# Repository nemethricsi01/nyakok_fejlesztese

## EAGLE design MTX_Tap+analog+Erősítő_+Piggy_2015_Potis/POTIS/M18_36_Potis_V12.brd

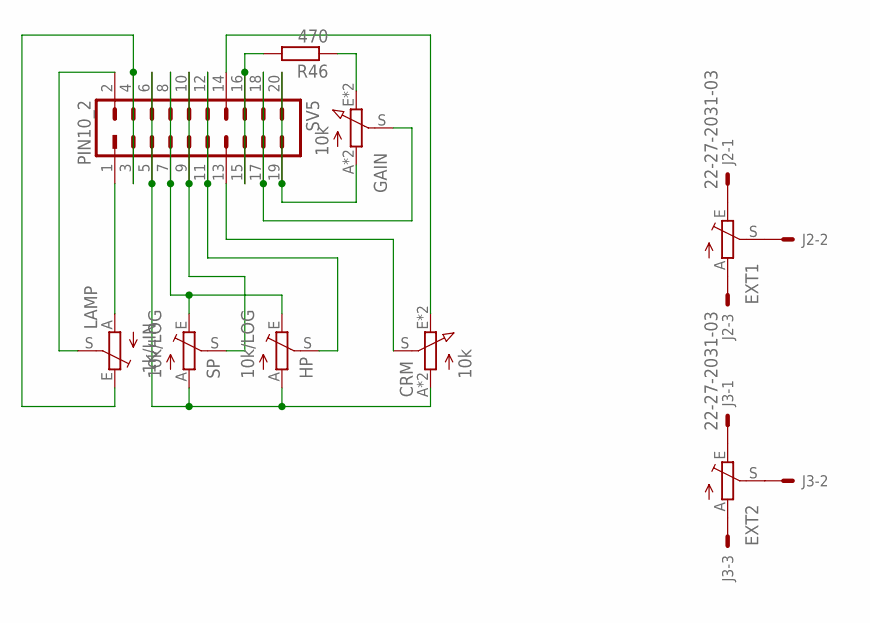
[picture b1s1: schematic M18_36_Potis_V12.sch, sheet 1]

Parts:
CRM: 10k; P_PT-10+15_KIEMELT
EXT1, EXT2: TRIM_EU-PT10; PT-10
GAIN: 10k; P_PT-10+15_KIEMELT
HP: 10k/LOG; POT_NAR
J2, J3: 22-27-2031-03; 6410-03
LAMP: 1k/LIN; POT_NAR
R46: 470; R0805
SP: 10k/LOG; POT_NAR
SV5: PIN10_2

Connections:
unnamed: CRM.S, SV5.13
unnamed: CRM.A, CRM.A1 (A), HP.A, SP.A, SV5.5, SV5.6
unnamed: HP.E, SP.E, SV5.7, SV5.8
unnamed: SP.S, SV5.9, SV5.10
unnamed: EXT1.S, J2.2
unnamed: EXT2.S, J3.2
unnamed: EXT1.E, J2.1
unnamed: EXT1.A, J2.3
unnamed: LAMP.S, SV5.2
unnamed: EXT2.A, J3.3
unnamed: EXT2.E, J3.1
unnamed: LAMP.E, SV5.3, SV5.4
unnamed: HP.S, SV5.11, SV5.12
unnamed: LAMP.A, SV5.1
unnamed: CRM.E, CRM.E1 (E), SV5.14
unnamed: R46.2, SV5.15, SV5.16
unnamed: GAIN.S, SV5.17, SV5.18
unnamed: GAIN.A, GAIN.A1 (A), SV5.19, SV5.20
unnamed: GAIN.E, GAIN.E1 (E), R46.1

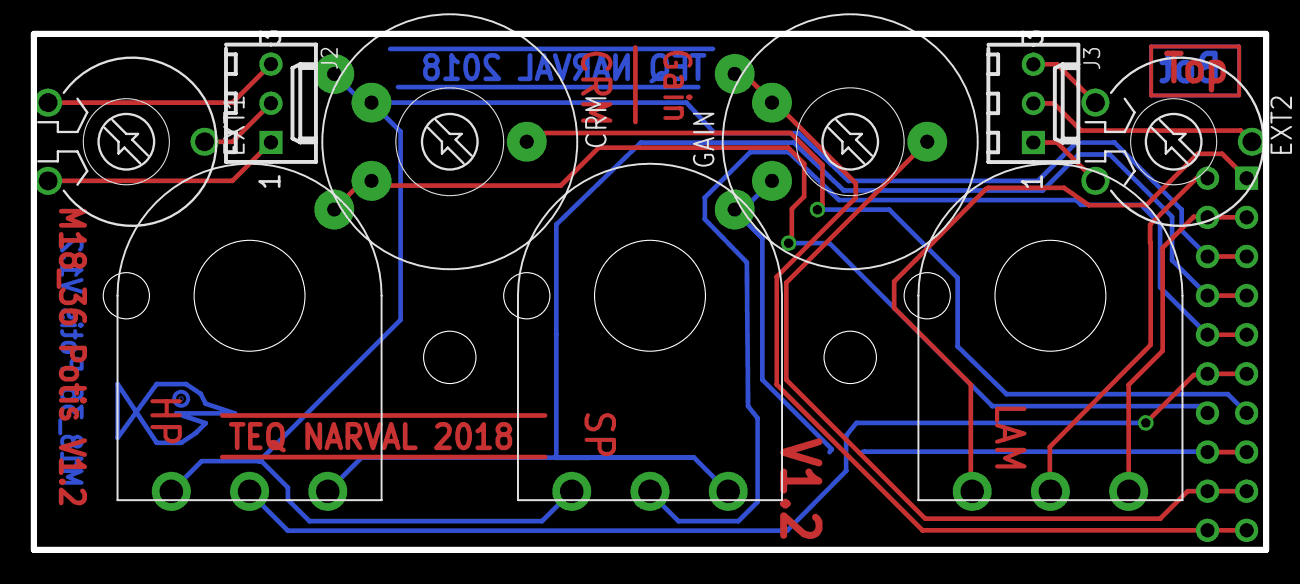
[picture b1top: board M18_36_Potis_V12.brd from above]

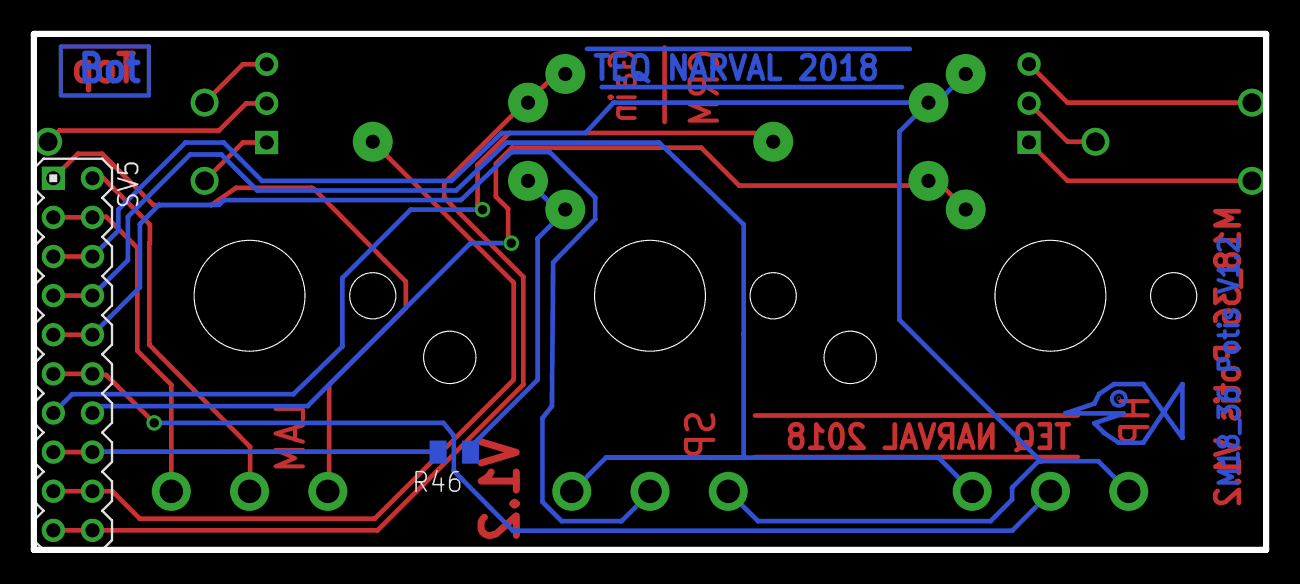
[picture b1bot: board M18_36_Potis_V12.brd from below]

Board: 2 copper layers, 80.0 x 33.5 mm, 11 parts (2 on the bottom side), 19 nets.

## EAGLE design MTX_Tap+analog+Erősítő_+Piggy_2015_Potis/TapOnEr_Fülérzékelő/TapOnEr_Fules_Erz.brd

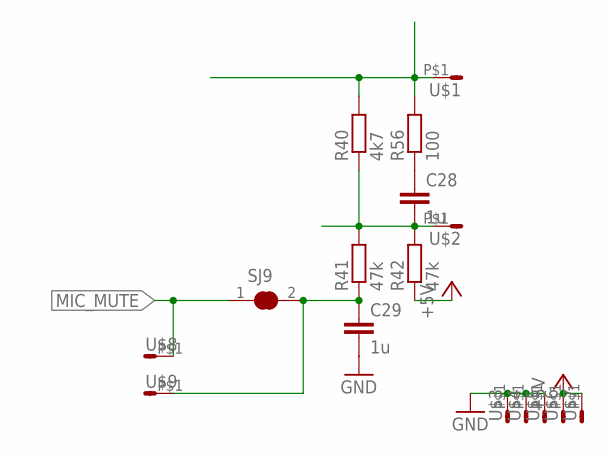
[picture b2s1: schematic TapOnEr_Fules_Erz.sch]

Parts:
C28, C29: 1u; C0805
R40: 4k7; R0805
R41, R42: 47k; R0805
R56: 100; R0805
SJ9: SJC
U$1, U$2, U$3, U$4, U$5, U$6, U$7, U$8, U$9: PADSMD; PAD_SMD

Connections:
+5V: R42.1, U$6.P$1, U$7.P$1
AGND: R40.2, R56.2, U$1.P$1
GND: C29.2, U$3.P$1, U$4.P$1, U$5.P$1
MIC_MUTE: SJ9.1, U$8.P$1
unnamed: C28.1, R56.1
unnamed: C29.1, R41.1, SJ9.2, U$9.P$1
unnamed: C28.2, R40.1, R41.2, R42.2, U$2.P$1

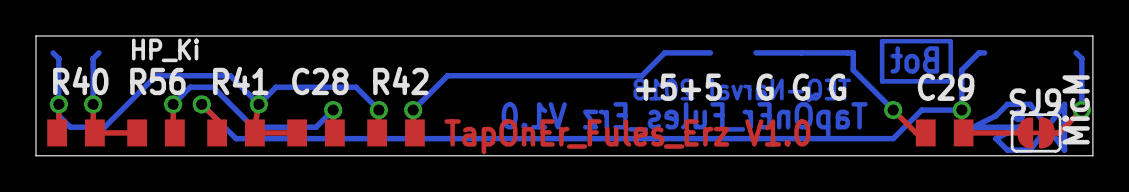
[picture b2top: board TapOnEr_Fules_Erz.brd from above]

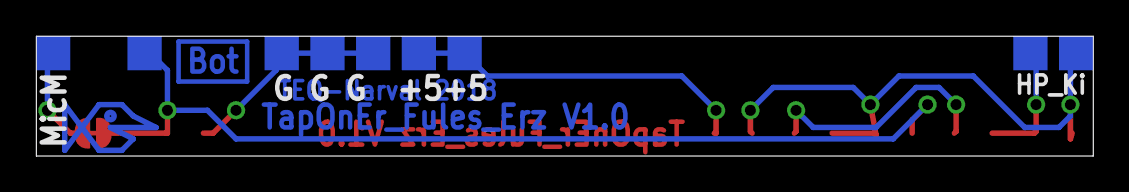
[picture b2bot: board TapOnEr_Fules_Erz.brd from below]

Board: 2 copper layers, 58.7 x 6.7 mm, 16 parts (9 on the bottom side), 7 nets.

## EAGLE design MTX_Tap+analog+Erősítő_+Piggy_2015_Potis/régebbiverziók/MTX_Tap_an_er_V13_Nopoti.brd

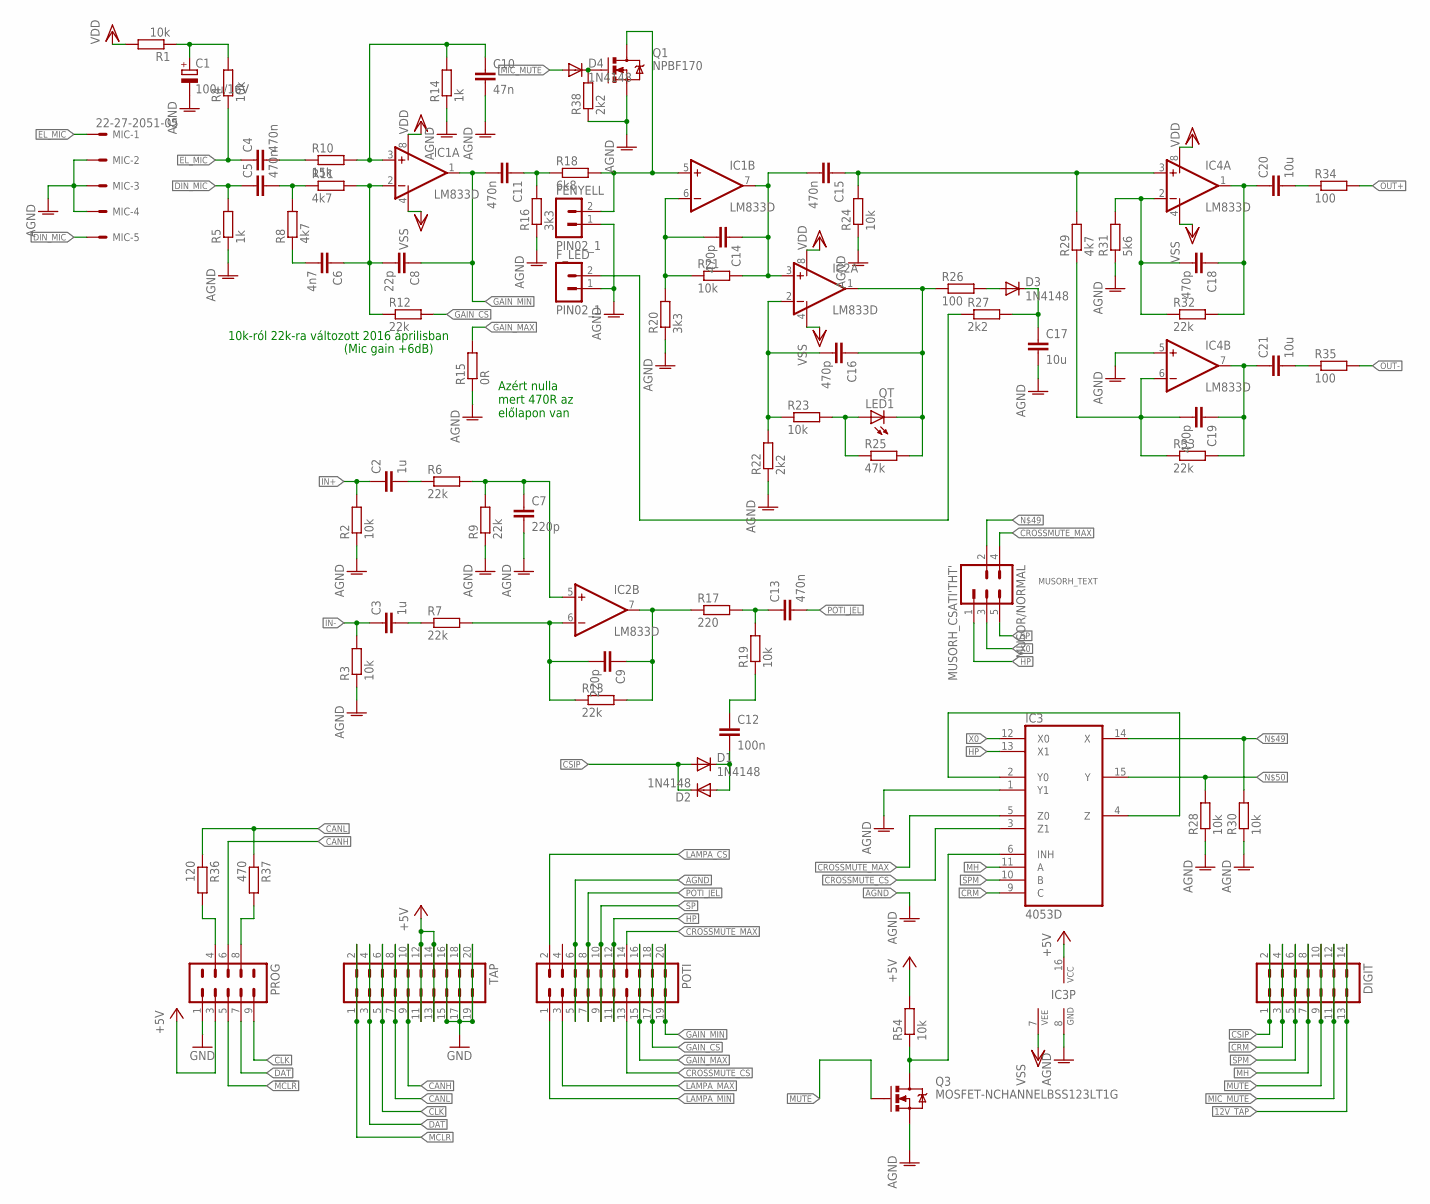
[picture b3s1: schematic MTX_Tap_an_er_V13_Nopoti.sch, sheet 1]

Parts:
C1: 100u/16V; E2,5-5
C2, C3: 1u; C0805
C4, C5, C11, C13, C15: 470n; C0805
C6: 4n7; C0805
C7, C9: 220p; C0805
C8: 22p; C0805
C10: 47n; C0805
C12: 100n; C0805
C14, C16, C18, C19: 470p; C0805
C17, C20, C21: 10u; C0805
D1, D2, D3, D4: 1N4148; SOD80C
DIGIT: MA07-2
FENYELL: PIN02_1
F_LED: PIN02_1
IC1, IC2, IC4: LM833D; SO08
IC3: 4053D; SO16
LED1: QT; LED3MM
MIC: 22-27-2051-05; 6410-05
MUSOR/NORMAL: MUSORH_CSATI'THT'; MUSORH_CSATI
POTI: MA10-2
PROG: CN_CANTAN
Q1: NPBF170; SOT23
Q3: MOSFET-NCHANNELBSS123LT1G; SOT23
R1, R2, R3, R4, R19, R21, R23, R24, R28, R30, R54: 10k; R0805
R5, R14: 1k; R0805
R6, R7, R9, R12, R13, R32, R33: 22k; R0805
R8, R11, R29: 4k7; R0805
R10: 15k; R0805
R15: 0R; R0805
R16, R20: 3k3; R0805
R17: 220; R0805
R18: 6k8; R0805
R22, R27, R38: 2k2; R0805
R25: 47k; R0805
R26, R34, R35: 100; R0805
R31: 5k6; R0805
R36: 120; R0805
R37: 470; R0805
TAP: MA10-2
U$1: MUSORH_TEXT

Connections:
1.: C9.1, IC2.7 (OUT), R13.2, R17.1
12V_TAP: DIGIT.13, DIGIT.14; also elsewhere on the board
!MCLR: PROG.5, TAP.1, TAP.2
+5V: IC3.16 (VCC), PROG.3, R54.2, TAP.11, TAP.12, TAP.13, TAP.14; also elsewhere on the board
AGND: C1.-, C7.2, C10.2, C17.2, FENYELL.1, F_LED.1, IC3.1 (Y1), IC3.8 (GND), IC4.5 (+IN), MIC.2, MIC.3, MIC.4, POTI.5, POTI.6, Q1.2 (S), Q3.2 (S), R2.1, R3.1, R5.1, R9.1, R14.1, R15.1, R16.1, R20.1, R22.1, R24.1, R28.1, R30.1, R31.1, R38.1; also elsewhere on the board
CANH: PROG.6, TAP.9, TAP.10; also elsewhere on the board
CANL: R36.1, R37.1, TAP.7, TAP.8; also elsewhere on the board
CLK: PROG.9, TAP.5, TAP.6
CRM: DIGIT.3, DIGIT.4, IC3.9 (C)
CROSSMUTE_CS: IC3.3 (Z1), POTI.13
CROSSMUTE_MAX: IC3.5 (Z0), MUSOR/NORMAL.4, POTI.14
CSIP: D1.A, D2.C, DIGIT.1, DIGIT.2
DAT: PROG.7, TAP.3, TAP.4
DIN_MIC: C5.1, MIC.5, R5.2
EL_MIC: C4.1, MIC.1, R4.1
GAIN_CS: POTI.17, POTI.18, R12.2
GAIN_MAX: POTI.15, POTI.16, R15.2
GAIN_MIN: C8.1, C11.2, IC1.1 (OUT), POTI.19, POTI.20
GND: PROG.1, TAP.15, TAP.16, TAP.17, TAP.18, TAP.19, TAP.20; also elsewhere on the board
HP: IC3.13 (X1), MUSOR/NORMAL.1, POTI.11, POTI.12
IN+: C2.1, R2.2; also elsewhere on the board
IN-: C3.1, R3.2; also elsewhere on the board
LAMPA_CS: POTI.2; also elsewhere on the board
LAMPA_MAX: POTI.3; also elsewhere on the board
LAMPA_MIN: POTI.1; also elsewhere on the board
MH: DIGIT.7, DIGIT.8, IC3.11 (A)
MIC_MUTE: D4.A, DIGIT.11, DIGIT.12
MUTE: DIGIT.9, DIGIT.10, Q3.1 (G)
unnamed: C1.+, R1.1, R4.2
unnamed: C4.2, R10.1
unnamed: C5.2, R8.2, R11.1
unnamed: C10.1, IC1.3 (+IN), R10.2, R14.2
unnamed: C6.1, C8.2, IC1.2 (-IN), R11.2, R12.1
unnamed: C6.2, R8.1
unnamed: FENYELL.2, IC1.5 (+IN), Q1.3 (D), R18.2
unnamed: IC3.2 (Y0), IC3.4 (Z)
unnamed: C11.1, R16.2, R18.1
unnamed: C18.2, IC4.2 (-IN), R31.2, R32.1
unnamed: C18.1, C20.1, IC4.1 (OUT), R32.2
unnamed: C14.2, IC1.6 (-IN), R20.2, R21.1
unnamed: C14.1, C15.2, IC1.7 (OUT), IC2.3 (+IN), R21.2
unnamed: C16.2, IC2.2 (-IN), R22.2, R23.1
unnamed: C19.2, IC4.6 (-IN), R29.1, R33.1
unnamed: LED1.A, R23.2, R25.1
unnamed: C16.1, IC2.1 (OUT), LED1.K (C), R25.2, R26.1
unnamed: D3.A, R26.2
unnamed: C17.1, D3.C, R27.2
unnamed: F_LED.2, R27.1
unnamed: C15.1, IC4.3 (+IN), R24.2, R29.2
unnamed: C19.1, C21.1, IC4.7 (OUT), R33.2
unnamed: C21.2, R35.1
unnamed: C20.2, R34.1
unnamed: C2.2, R6.1
unnamed: D4.C, Q1.1 (G), R38.2
unnamed: C7.1, IC2.5 (+IN), R6.2, R9.2
unnamed: C3.2, R7.1
unnamed: C12.2, D1.C, D2.A
unnamed: C9.2, IC2.6 (-IN), R7.2, R13.1
unnamed: C13.1, R17.2, R19.2
unnamed: C12.1, R19.1
unnamed 75: IC3.14 (X), MUSOR/NORMAL.2, R30.2; also elsewhere on the board
unnamed 76: IC3.15 (Y), R28.2; also elsewhere on the board
unnamed: PROG.8, R37.2
unnamed: PROG.4, R36.2
unnamed: IC3.6 (INH), Q3.3 (D), R54.1
OUT+: R34.2; also elsewhere on the board
OUT-: R35.2; also elsewhere on the board
POTI_JEL: C13.2, POTI.7, POTI.8
SP: MUSOR/NORMAL.5, POTI.9, POTI.10
SPM: DIGIT.5, DIGIT.6, IC3.10 (B)
VDD: IC1.8 (V+), IC2.8 (V+), IC4.8 (V+), R1.2; also elsewhere on the board
VSS: IC1.4 (V-), IC2.4 (V-), IC3.7 (VEE), IC4.4 (V-); also elsewhere on the board
X0: IC3.12 (X0), MUSOR/NORMAL.3

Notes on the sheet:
10k-ról 22k-ra változott 2016 áprilisban
(Mic gain +6dB)
Azért nulla mert 470R az előlapon van

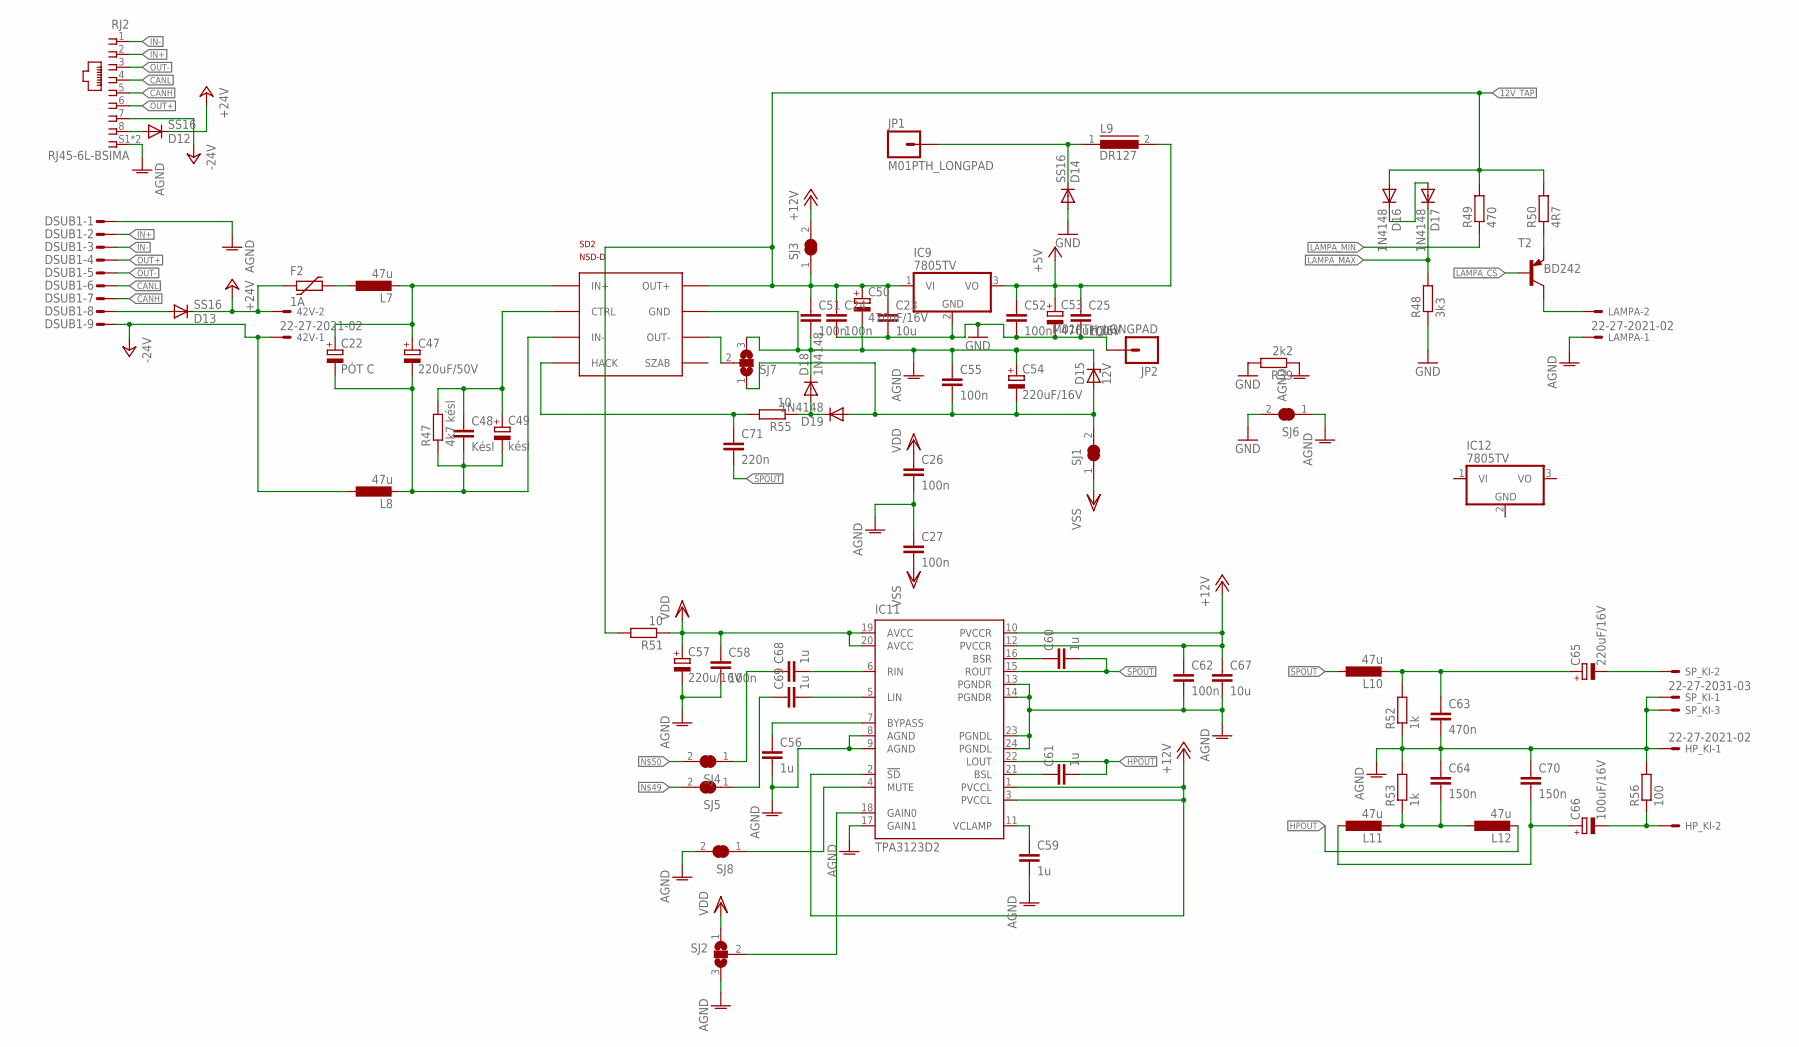
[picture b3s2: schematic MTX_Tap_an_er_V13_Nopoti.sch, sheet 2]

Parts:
42V: 22-27-2021-02; 6410-02
C22: PÓT C; E3,5-8
C23, C67: 10u; C0805
C24, C25, C26, C27, C51, C52, C55, C58, C62: 100n; C0805
C47: 220uF/50V; E3,5-8
C48: Késl; C0805
C49: késl; E2,5-5
C50, C53: 470uF/16V; E3,5-8
C54, C65: 220uF/16V; E2,5-7
C56, C59, C60, C61, C68, C69: 1u; C0805
C57: 220u/16V; E2,5-7
C63: 470n; C0805
C64, C70: 150n; C0805
C66: 100uF/16V; E2,5-6
C71: 220n; C0805
D12, D13, D14: SS16; DO-214AC
D15: 12V; SOD80C
D16, D17, D18, D19: 1N4148; SOD80C
DSUB1: M09-182S; 182-009-MALE
F2: 1A; PTC1812L
HP_KI: 22-27-2021-02; 6410-02
IC9, IC12: 7805TV; TO220V
IC11: TPA3123D2; PWP-TSSOP24
JP1, JP2: M01PTH_LONGPAD; 1X01_LONGPAD
L7, L8, L10, L11, L12: 47u; PIS2816
L9: DR127
LAMPA: 22-27-2021-02; 6410-02
R39: 2k2; R0805
R47: 4k7 késl; R0805
R48: 3k3; R0805
R49: 470; R0805
R50: 4R7; R0805
R51: 10; R1210
R52, R53: 1k; R0805
R55: 10; R0805
R56: 100; R0805
RJ2: RJ45-6L-BSIMA; RJ45
SD2: NSD-D
SJ1, SJ3, SJ4, SJ5, SJ6, SJ8: SOLDERJUMPER_CLOSED; SOLDERJUMPER_CLOSEDWIRE
SJ2: SJ2WW12; SJ_2W_12
SJ7: SJ2WW23; SJ_2W_23
SP_KI: 22-27-2031-03; 6410-03
T2: BD242; TO220V

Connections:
12V_TAP: C23.1, C24.1, C50.+, C51.1, D16.A, IC9.1 (VI), R49.2, R50.2, R51.2, SD2.OUT+, SJ3.1; also elsewhere on the board
+5V: C25.1, C52.1, C53.+, IC9.3 (VO), L9.2; also elsewhere on the board
+12V: C62.1, C67.1, IC11.1 (PVCCL), IC11.2 (!SD), IC11.3 (PVCCL), IC11.10 (PVCCR), IC11.12 (PVCCR), SJ3.2
+24V: 42V.2, D12.1 (C), D13.1 (C), F2.1
-24V: 42V.1, DSUB1.9, L8.1, RJ2.7
AGND: C26.2, C27.1, C50.-, C51.2, C54.+, C55.1, C56.2, C57.-, C58.2, C59.2, C62.2, C63.2, C64.1, C67.2, C70.1, D15.C, D18.C, DSUB1.1, HP_KI.1, IC11.8 (AGND), IC11.9 (AGND), IC11.13 (PGNDR), IC11.14 (PGNDR), IC11.17 (GAIN1), IC11.23 (PGNDL), IC11.24 (PGNDL), LAMPA.1, R39.1, R52.1, R53.2, R56.2, RJ2.S1 (S), RJ2.S2 (S), SD2.COMMON (GND), SJ2.3, SJ6.1, SJ7.3, SJ8.2, SP_KI.1, SP_KI.3; also elsewhere on the board
CANH: DSUB1.7, RJ2.5; also elsewhere on the board
CANL: DSUB1.6, RJ2.4; also elsewhere on the board
GND: C23.2, C24.2, C25.2, C52.2, C53.-, D14.2 (A), IC9.2 (GND), JP2.1, R39.2, R48.1, SJ6.2; also elsewhere on the board
HPIN_X: C69.1, SJ5.1
HPOUT: C61.2, IC11.22 (LOUT), L12.2
IN+: DSUB1.2, RJ2.2; also elsewhere on the board
IN-: DSUB1.3, RJ2.1; also elsewhere on the board
LAMPA_CS: T2.1 (B); also elsewhere on the board
LAMPA_MAX: D17.C, R48.2; also elsewhere on the board
LAMPA_MIN: R49.1; also elsewhere on the board
unnamed: C54.-, C55.2, D15.A, D19.A, SJ1.2, SJ7.1
unnamed: D12.2 (A), RJ2.8
unnamed: C65.-, SP_KI.2
unnamed: SD2.OUT-, SJ7.2
unnamed 75: SJ5.2; also elsewhere on the board
unnamed 76: SJ4.2; also elsewhere on the board
unnamed: C71.1, R55.2, SD2.HACK
unnamed: D13.2 (A), DSUB1.8
unnamed: F2.2, L7.1
unnamed: C22.+, C47.+, L7.2, SD2.INPUT+ (IN+)
unnamed: C48.1, C49.+, R47.2, SD2.CONTROL (CTRL)
unnamed: C22.-, C47.-, C48.2, C49.-, L8.2, R47.1, SD2.INPUT- (IN-)
unnamed: D14.1 (C), JP1.1, L9.1
unnamed: R50.1, T2.3 (E)
unnamed: D16.C, D17.A
unnamed: LAMPA.2, T2.2 (C)
unnamed: C56.1, IC11.7 (BYPASS)
unnamed: C59.1, IC11.11 (VCLAMP)
unnamed: C61.1, IC11.21 (BSL)
unnamed: C60.1, IC11.16 (BSR)
unnamed: C63.1, C65.+, L10.2, R52.2
unnamed: C64.2, L11.2, L12.1, R53.1
unnamed: C66.-, HP_KI.2, R56.1
unnamed: C68.2, IC11.6 (RIN)
unnamed: C69.2, IC11.5 (LIN)
unnamed: IC11.18 (GAIN0), SJ2.2
unnamed: IC11.4 (MUTE), SJ8.1
unnamed: D18.A, D19.C, R55.1
unnamed: C66.+, C70.2, L11.1
OUT+: DSUB1.4, RJ2.6; also elsewhere on the board
OUT-: DSUB1.5, RJ2.3; also elsewhere on the board
SPIN_X: C68.1, SJ4.1
SPOUT: C60.2, C71.2, IC11.15 (ROUT), L10.1
VDD: C26.1, C57.+, C58.1, IC11.19 (AVCC), IC11.20 (AVCC), R51.1, SJ2.1; also elsewhere on the board
VSS: C27.2, SJ1.1; also elsewhere on the board

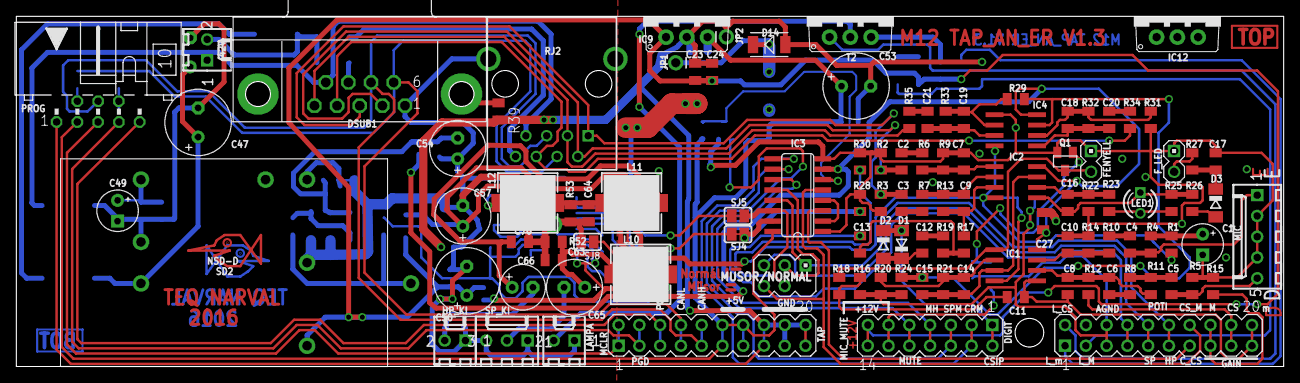
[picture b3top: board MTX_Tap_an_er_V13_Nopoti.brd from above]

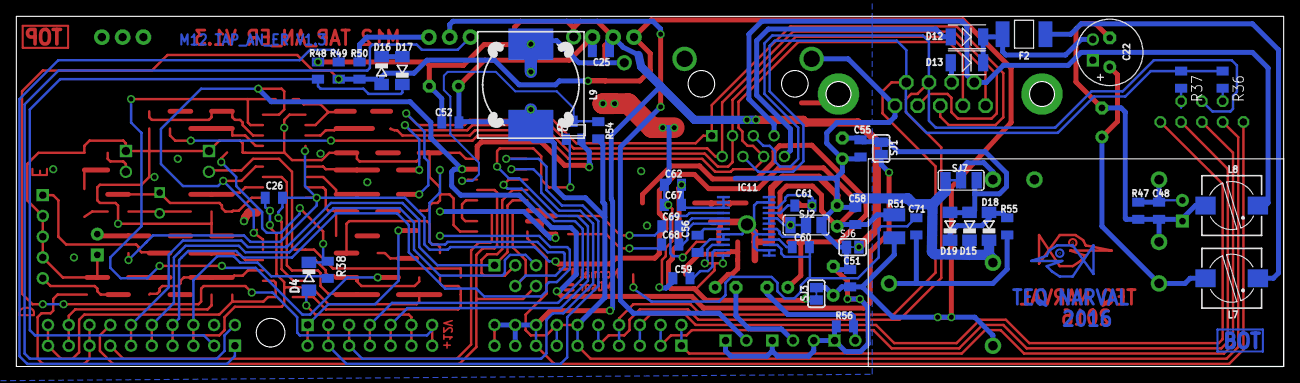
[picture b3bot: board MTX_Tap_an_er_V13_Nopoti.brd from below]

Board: 2 copper layers, 155.0 x 42.8 mm, 157 parts (47 on the bottom side), 107 nets.

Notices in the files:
parts and their libraries:
SparkFun-DiscreteSemi: Licensing: Creative Commons ShareAlike 4.0 International - https://creativecommons.org/licenses/by-sa/4.0
microbuilder: This work is placed in the public domain, and may be freely used for commercial and non-commercial work with the following conditions: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
